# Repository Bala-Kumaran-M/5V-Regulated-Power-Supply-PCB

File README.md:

# 5V-Regulated-Power-Supply-PCB
5V regulated power supply PCB designed using KiCad for stable power delivery to electronic circuits.

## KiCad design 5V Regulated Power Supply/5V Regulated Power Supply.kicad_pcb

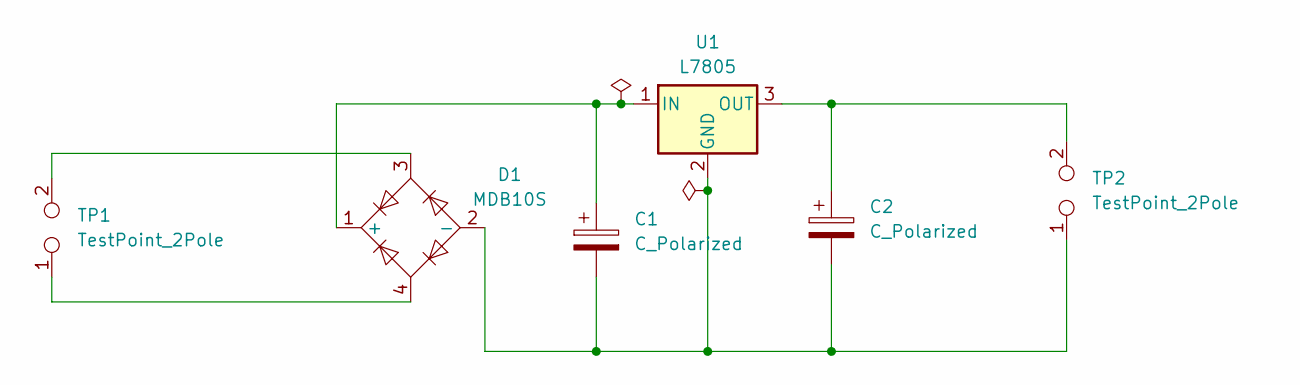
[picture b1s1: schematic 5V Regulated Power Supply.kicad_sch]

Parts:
C1, C2: C_Polarized; CP_Radial_D5.0mm_P2.50mm
D1: MDB10S; TSSOP-4_4.4x5mm_P4mm
TP1, TP2: TestPoint_2Pole; TestPoint_2Pads_Pitch2.54mm_Drill0.8mm
U1: L7805; TO-220-3_Vertical

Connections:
unnamed: C1.1, D1.1 (+), U1.1 (IN)
unnamed: C1.2, C2.2, D1.2 (-), TP2.1, U1.2 (GND)
unnamed: D1.3, TP1.2
unnamed: D1.4, TP1.1
unnamed: C2.1, TP2.2, U1.3 (OUT)

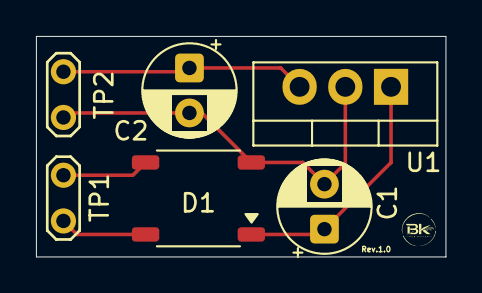
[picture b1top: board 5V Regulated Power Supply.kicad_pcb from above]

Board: 2 copper layers, 22.8 x 12.2 mm, 6 parts (0 on the bottom side), 5 nets.
